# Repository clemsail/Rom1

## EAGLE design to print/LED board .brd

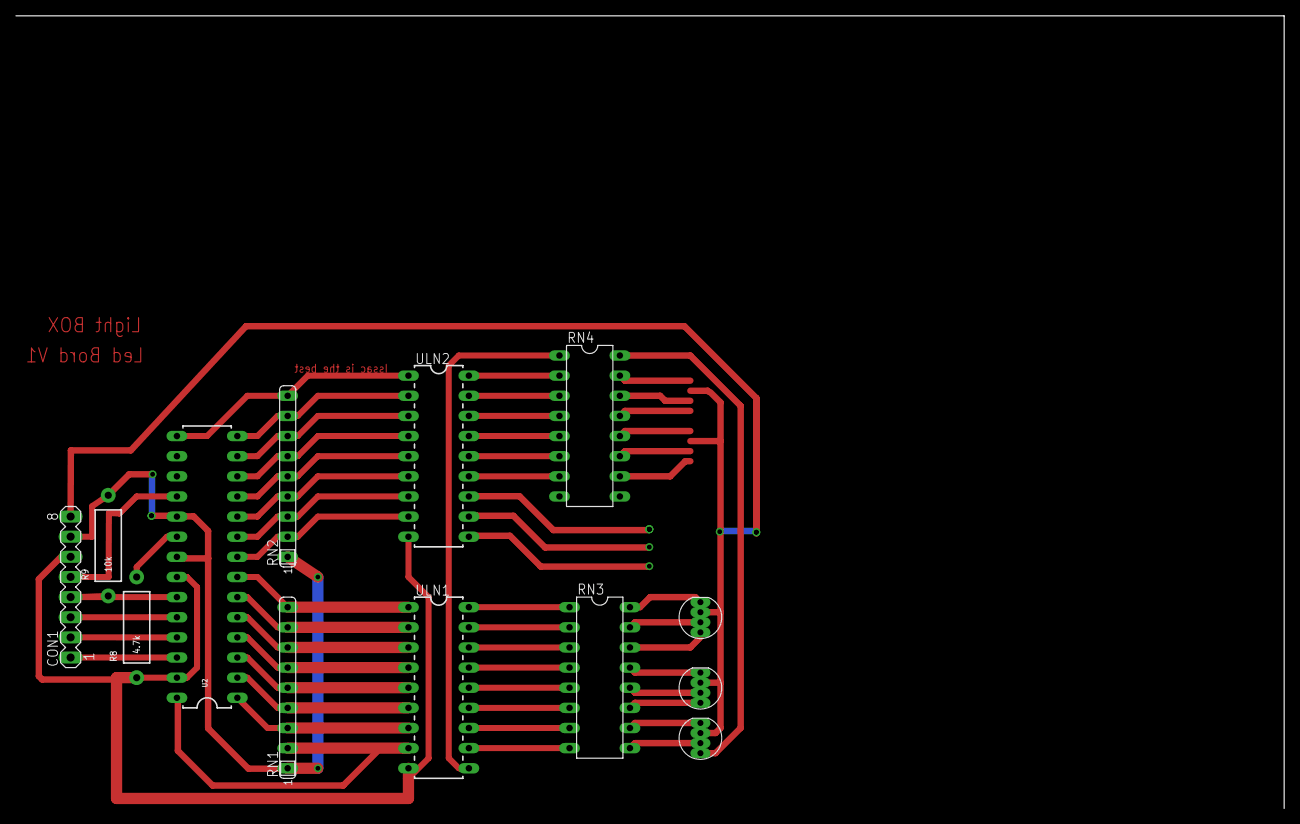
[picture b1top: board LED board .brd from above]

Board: 2 copper layers, 160.0 x 100.0 mm, 13 parts (0 on the bottom side), 49 nets.

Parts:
CON1: CON1; MA08-1
D1, D2, D3: LED-RGB-CA-THRUCLEAR; LED-RGB-THRU
R8: 4.7k; AXIAL-0.5
R9: 10k; AXIAL-0.5
RN1, RN2: 10k; SIL9
RN3, RN4: 470; DIL16
U2: TLC5940-NT; DIL28-3
ULN1, ULN2: ULN2803; DIL18

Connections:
GND: CON1.6, R8.P$1, U2.22, U2.27, ULN1.9, ULN2.9
unnamed: RN3.1, ULN1.18
unnamed: RN3.2, ULN1.17
unnamed: RN3.3, ULN1.16
unnamed: RN3.4, ULN1.15
unnamed: RN3.5, ULN1.14
unnamed: RN3.6, ULN1.13
unnamed: R8.P$2, U2.20
unnamed: CON1.4, R9.P$1, U2.23
unnamed: CON1.5, U2.18
unnamed: CON1.3, U2.24
unnamed: CON1.2, U2.25
unnamed: CON1.1, U2.26
unnamed: RN2.2, U2.8, ULN2.8
unnamed: RN1.2, U2.28, ULN1.8
unnamed: RN1.3, U2.1, ULN1.7
unnamed: RN1.4, U2.2, ULN1.6
unnamed: RN1.5, U2.3, ULN1.5
unnamed: RN1.6, U2.4, ULN1.4
unnamed: RN1.7, U2.5, ULN1.3
unnamed: RN1.8, U2.6, ULN1.2
unnamed: RN1.9, U2.7, ULN1.1
unnamed: RN2.3, U2.9, ULN2.7
unnamed: RN2.4, U2.10, ULN2.6
unnamed: RN2.5, U2.11, ULN2.5
unnamed: RN2.6, U2.12, ULN2.4
unnamed: RN2.7, U2.13, ULN2.3
unnamed: RN2.8, U2.14, ULN2.2
unnamed: RN2.9, U2.15, ULN2.1
unnamed: RN3.7, ULN1.12
unnamed: RN3.8, ULN1.11
unnamed: D1.1, RN3.16
unnamed: D1.3, RN3.15
unnamed: D1.4, RN3.14
unnamed: D2.1, RN3.13
unnamed: D2.3, RN3.12
unnamed: D2.4, RN3.11
unnamed: D3.1, RN3.10
unnamed: D3.3, RN3.9
unnamed: RN4.1, ULN1.10
unnamed: D3.4, RN4.16
unnamed: RN4.2, ULN2.18
unnamed: RN4.3, ULN2.17
unnamed: RN4.4, ULN2.16
unnamed: RN4.5, ULN2.15
unnamed: RN4.6, ULN2.14
unnamed: RN4.7, ULN2.13
VCC: CON1.7, R9.P$2, RN1.1, RN2.1, U2.19, U2.21
VCC+12: CON1.8, D1.2, D2.2, D3.2

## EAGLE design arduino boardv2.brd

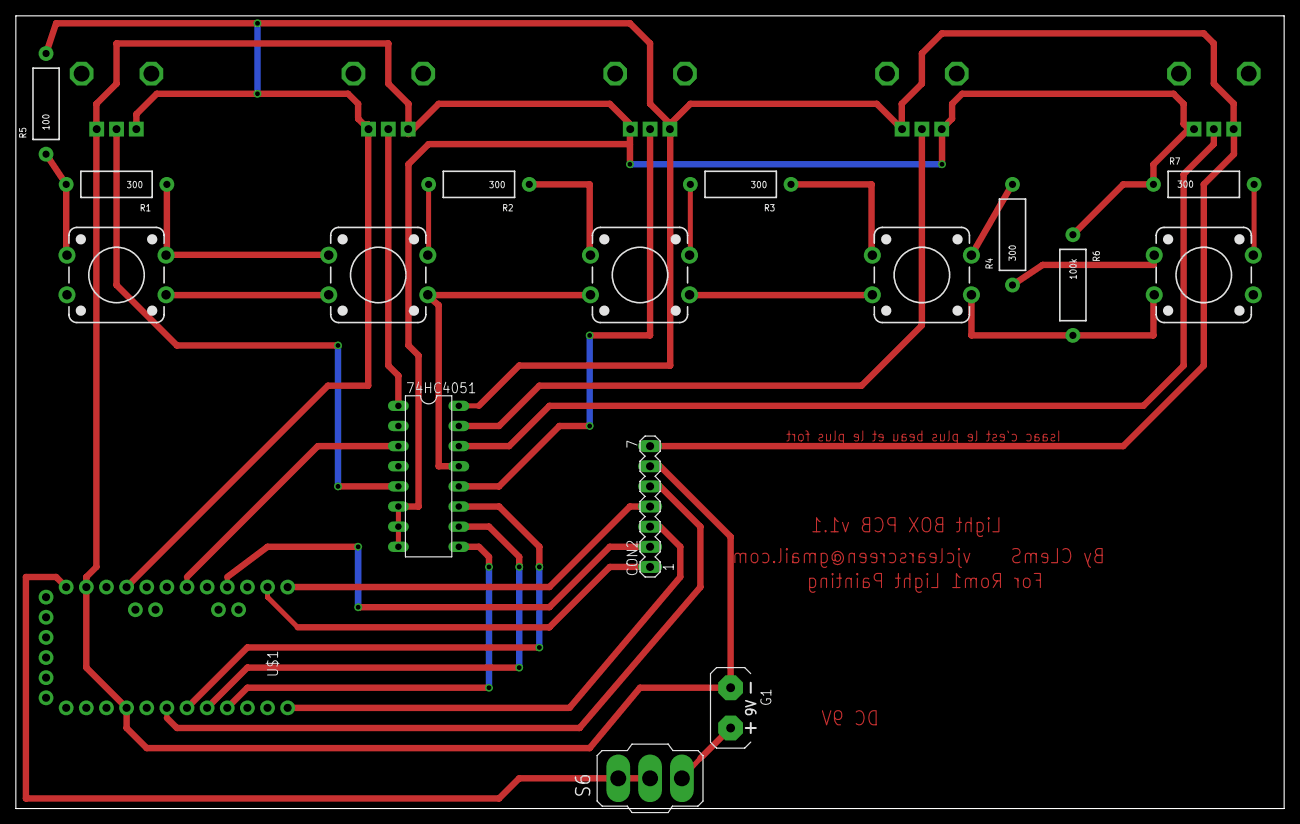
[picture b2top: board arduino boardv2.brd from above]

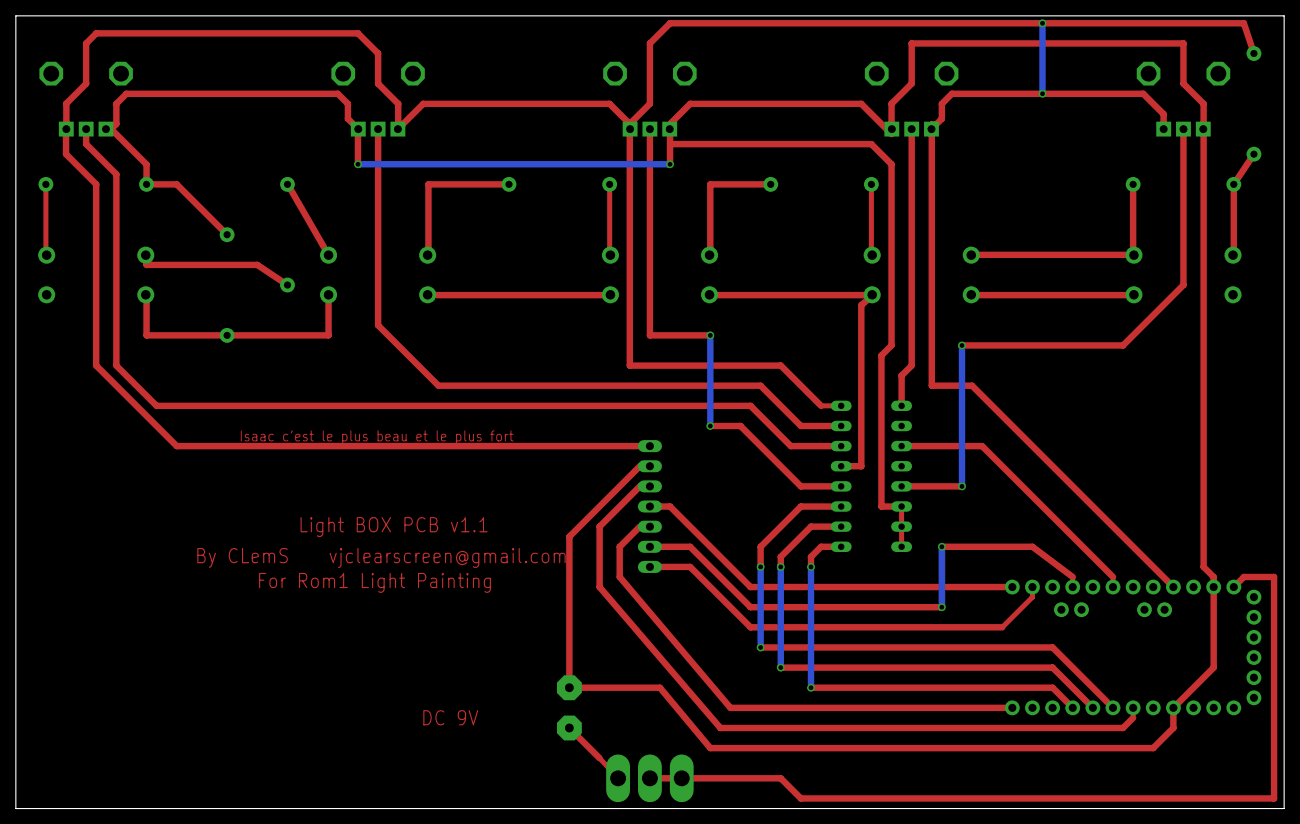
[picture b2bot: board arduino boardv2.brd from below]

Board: 2 copper layers, 160.0 x 100.0 mm, 22 parts (2 on the bottom side), 25 nets.

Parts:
74HC4051: 4051N; DIL16
CON2: CON2; MA07-1
G1: AB9V
R1, R2, R3, R4, R7: 300; AXIAL-0.5
R5: 100; AXIAL-0.5
R6: 100k; AXIAL-0.5
RV1, RV2, RV3, RV4, RV5: 1k; ALPS_POT
S1, S2, S3, S4, S5: SWITCH-MOMENTARY-212MM; TACTILE-PTH-12MM
S6: ON/OFF; 320-916
U$1: ARDUINO_PRO_MINI

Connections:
A1: 74HC4051.3, U$1.18
D3_GSCLK: CON2.5, U$1.6
D4_A_S0: 74HC4051.11, U$1.7
D5_B_S1: 74HC4051.10, U$1.8
D6_C_S2: 74HC4051.9, U$1.9
D9_XLAT: CON2.3, U$1.12
D10_BLANK: CON2.4, U$1.13
D11_SIN: CON2.1, U$1.14
D13_SCLK: CON2.2, U$1.16
GND: 74HC4051.6, 74HC4051.7, 74HC4051.8, CON2.6, G1.-, R6.P$1, R7.P$1, RV1.P$1, RV2.P$1, RV3.P$1, RV4.P$1, RV5.P$1, U$1.4, U$1.23
unnamed: S6.2, U$1.24
unnamed: R1.P$2, R5.P$1
unnamed: R4.P$2, S4.3
unnamed: G1.+, S6.3
POT1: 74HC4051.5, RV1.P$2
POT2: 74HC4051.1, RV2.P$2
POT3: 74HC4051.12, RV3.P$2
POT4: 74HC4051.15, RV4.P$2
POT5: 74HC4051.14, RV5.P$2
S$2: 74HC4051.13, S2.1
S$6: R2.P$2, S2.3
S$9: R3.P$2, S3.3
S$10: R7.P$2, S5.3
SWITCH_IN: R6.P$2, S4.1
VCC: 74HC4051.16, CON2.7, R5.P$2, RV1.P$3, RV2.P$3, RV3.P$3, RV4.P$3, RV5.P$3, U$1.21

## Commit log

2017-02-10 :octocat: Added .gitattributes & .gitignore files

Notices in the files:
parts and their libraries:
SparkFun-Electromechanical: Licensing: Creative Commons ShareAlike 4.0 International - https://creativecommons.org/licenses/by-sa/4.0
